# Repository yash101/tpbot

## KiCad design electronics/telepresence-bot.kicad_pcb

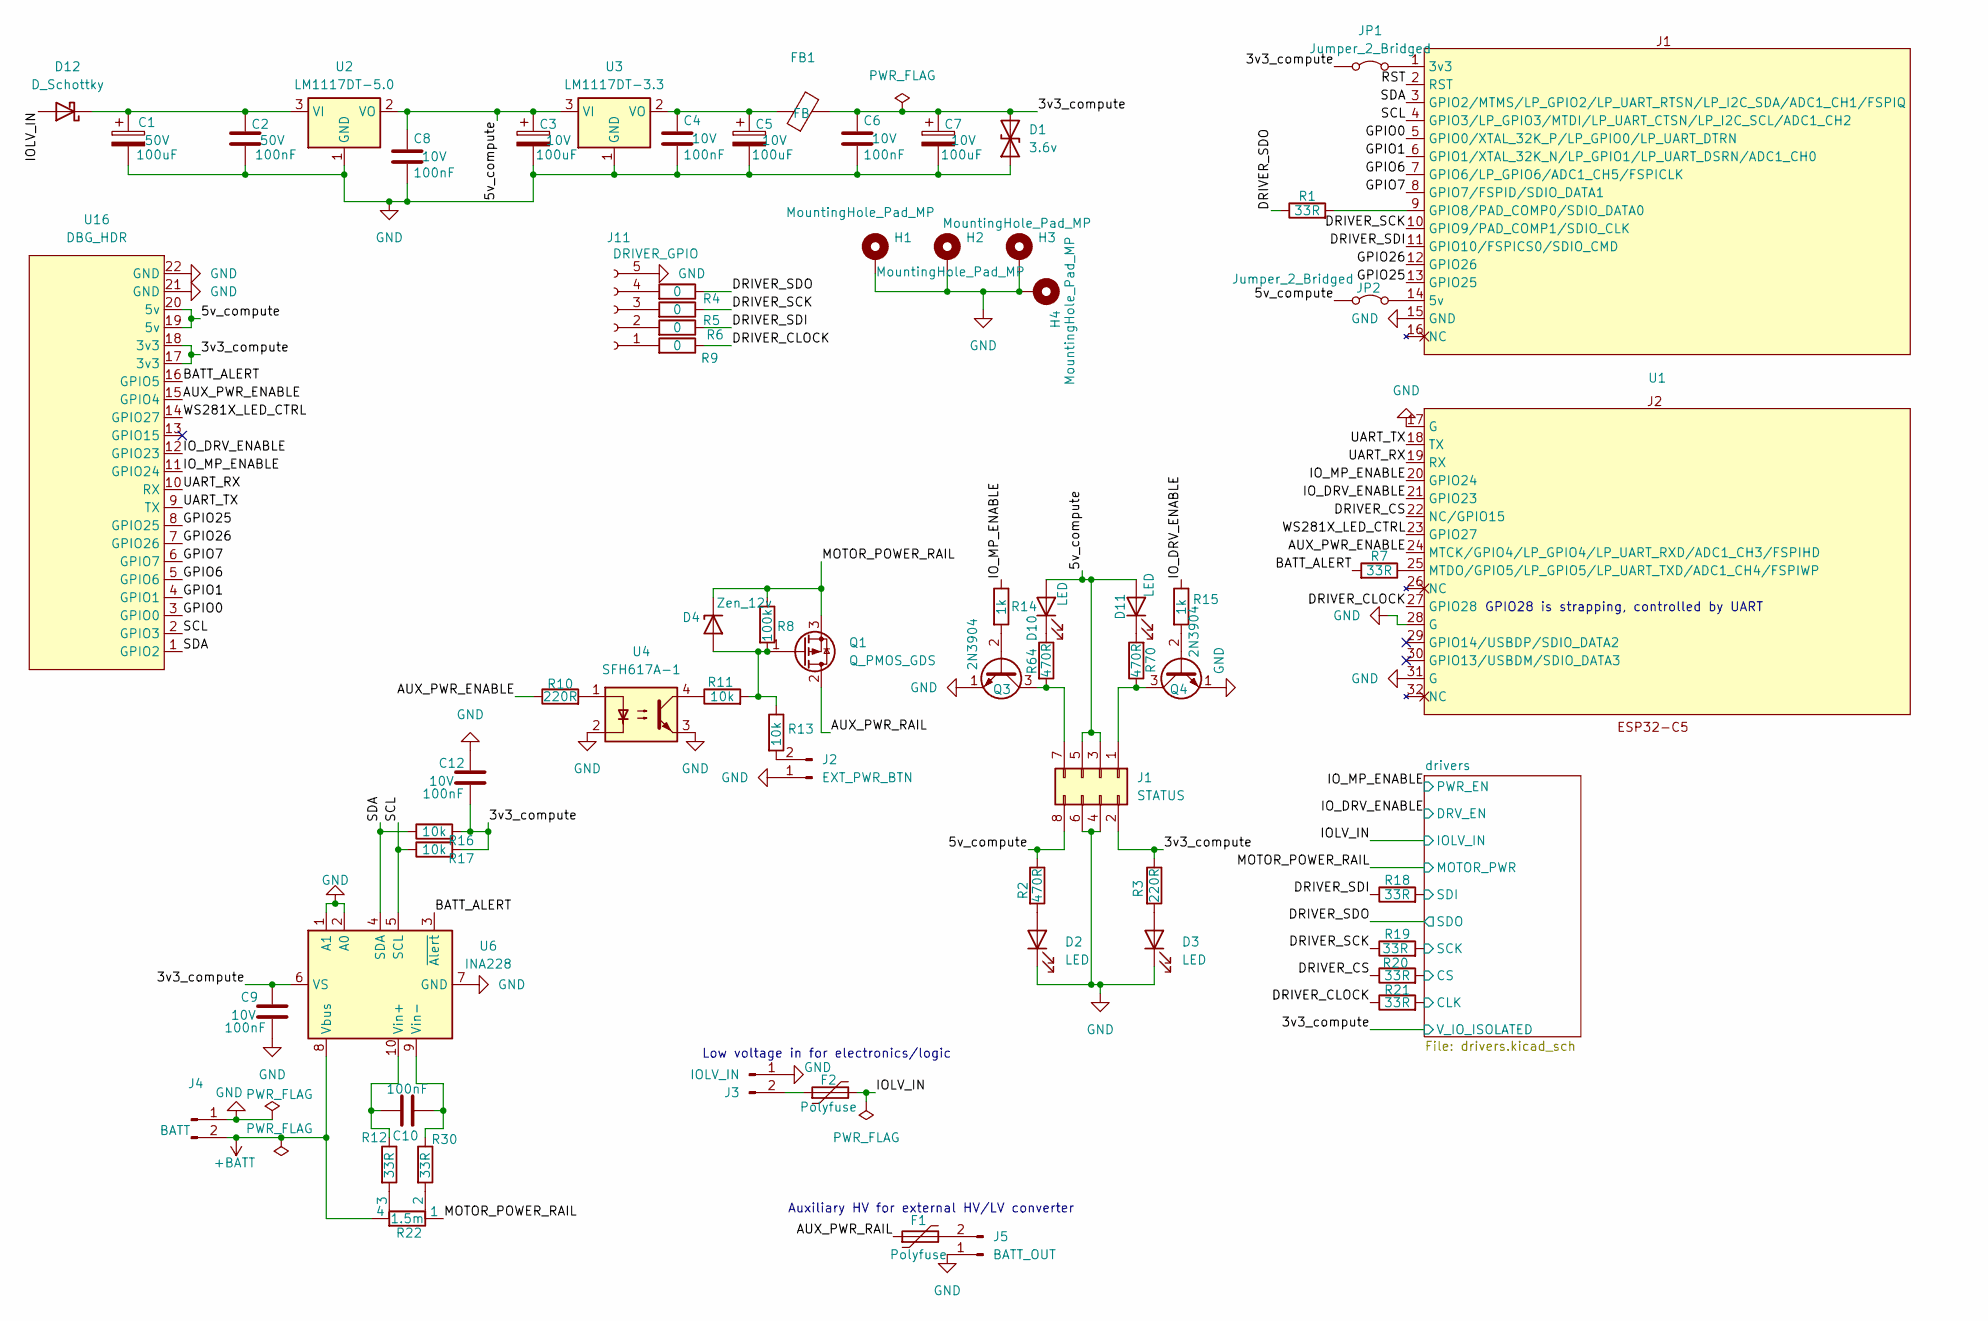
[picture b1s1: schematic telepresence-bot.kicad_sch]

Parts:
C1: 100uF; CP_Radial_D8.0mm_P5.00mm
C2, C10: 100nF; C_1206_3216Metric_Pad1.33x1.80mm_HandSolder
C3, C5, C7: 100uF; CP_Radial_D6.3mm_P2.50mm
C4, C6, C8, C9, C12: 100nF; C_0805_2012Metric_Pad1.18x1.45mm_HandSolder
D1: 3.6v; D_DO-41_SOD81_P2.54mm_Vertical_AnodeUp
D2, D3, D10, D11: LED; LED_D3.0mm
D4: Zen_12v; D_DO-41_SOD81_P2.54mm_Vertical_AnodeUp
D12: D_Schottky; D_DO-201AD_P5.08mm_Vertical_KathodeUp
F1, F2: Polyfuse; RV_Disc_D9mm_W5.2mm_P5mm
FB1: FB; L_1210_3225Metric_Pad1.42x2.65mm_HandSolder
H1, H2, H3, H4: MountingHole_Pad_MP; MountingHole_4.3mm_M4_ISO7380
J1: STATUS; PinSocket_2x04_P2.54mm_Vertical
J2: EXT_PWR_BTN; PinHeader_1x02_P2.54mm_Vertical
J3: IOLV_IN; PinHeader_1x02_P2.54mm_Vertical
J4: BATT; BATT_CONNECTOR
J5: BATT_OUT; PinSocket_1x02_P2.54mm_Vertical
J11: DRIVER_GPIO; PinSocket_1x05_P2.54mm_Vertical
JP1, JP2: Jumper_2_Bridged; PinSocket_1x02_P2.54mm_Vertical
Q1: Q_PMOS_GDS; TO-220-3_Vertical
Q3, Q4: 2N3904; TO-92_Inline_Wide
R1, R7, R12, R18, R19, R20, R21, R30: 33R; R_0805_2012Metric_Pad1.20x1.40mm_HandSolder
R2, R64, R70: 470R; R_Axial_DIN0204_L3.6mm_D1.6mm_P1.90mm_Vertical
R3, R10: 220R; R_Axial_DIN0204_L3.6mm_D1.6mm_P1.90mm_Vertical
R4, R5, R6, R9: 0; SolderJumper-2_P1.3mm_Open_Pad1.0x1.5mm
R8: 100k; R_0805_2012Metric_Pad1.20x1.40mm_HandSolder
R11, R13, R16, R17: 10k; R_0805_2012Metric_Pad1.20x1.40mm_HandSolder
R14, R15: 1k; R_Axial_DIN0204_L3.6mm_D1.6mm_P1.90mm_Vertical
R22: 1.5m; R_Shunt_Vishay_WSKW0612
U1: ESP32-C5-DevKitC-1-v1.2
U2: LM1117DT-5.0; TO-220-3_Vertical
U3: LM1117DT-3.3; TO-220-3_Vertical
U4: SFH617A-1; DIP-4_W7.62mm
U6: INA228; VSSOP-10_3x3mm_P0.5mm
U16: DBG_HDR; PinSocket_2x11_P2.54mm_Vertical

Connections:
+BATT: J4.2, R22.4, U6.8 (Vbus)
/3v3_compute: C6.1, C7.1, C9.1, C12.2, D1.2 (A2), FB1.2, J1.2, JP1.1 (A), R3.1, R16.2, R17.2, U6.6 (VS), U16.17 (3v3), U16.18 (3v3); also elsewhere on the board
/5v_compute: C3.1, C8.1, D10.2 (A), D11.2 (A), J1.3, J1.5, J1.8, JP2.1 (A), R2.1, U2.2 (VO), U3.3 (VI), U16.19 (5v), U16.20 (5v)
/AUX_PWR_ENABLE: R10.1, U1.24 (MTCK/GPIO4/LP_GPIO4/LP_UART_RXD/ADC1_CH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), U16.15 (GPIO4)
/AUX_PWR_RAIL: F1.1, Q1.2 (D)
/BATT_ALERT: R7.2, U6.3 (~Alert), U16.16 (GPIO5)
/DRIVER_CLOCK: R9.1, R21.1, U1.27 (GPIO28)
/DRIVER_CS: R20.1, U1.22 (NC/GPIO15)
/DRIVER_SCK: R5.1, R19.1, U1.10 (GPIO9/PAD_COMP1/SDIO_CLK)
/DRIVER_SDI: R6.1, R18.1, U1.11 (GPIO10/FSPICS0/SDIO_CMD)
/DRIVER_SDO: R1.1, R4.1; also elsewhere on the board
/GPIO0: U1.5 (GPIO0/XTAL_32K_P/LP_GPIO0/LP_UART_DTRN), U16.3 (GPIO0)
/GPIO1: U1.6 (GPIO1/XTAL_32K_N/LP_GPIO1/LP_UART_DSRN/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), U16.4 (GPIO1)
/GPIO6: U1.7 (GPIO6/LP_GPIO6/ADC1_CH5/FSPICLK), U16.5 (GPIO6)
/GPIO7: U1.8 (GPIO7/FSPID/SDIO_DATA1), U16.6 (GPIO7)
/GPIO25: U1.13 (GPIO25), U16.8 (GPIO25)
/GPIO26: U1.12 (GPIO26), U16.7 (GPIO26)
/IOLV_IN: D12.2 (A), F2.2; also elsewhere on the board
/IO_DRV_ENABLE: R15.1, U1.21 (GPIO23), U16.12 (GPIO23); also elsewhere on the board
/IO_MP_ENABLE: R14.1, U1.20 (GPIO24), U16.11 (GPIO24); also elsewhere on the board
/MOTOR_POWER_RAIL: D4.1 (K), Q1.3 (S), R8.1, R22.1; also elsewhere on the board
/RST: U1.2 (RST)
/SCL: R17.1, U1.4 (GPIO3/LP_GPIO3/MTDI/LP_UART_CTSN/LP_I2C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), U6.5 (SCL), U16.2 (GPIO3)
/SDA: R16.1, U1.3 (GPIO2/MTMS/LP_GPIO2/LP_UART_RTSN/LP_I2C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), U6.4 (SDA), U16.1 (GPIO2)
/UART_RX: U1.19 (RX), U16.10 (RX)
/UART_TX: U1.18 (TX), U16.9 (TX)
/WS281X_LED_CTRL: U1.23 (GPIO27), U16.14 (GPIO27)
/drivers/CLK: R21.2; also elsewhere on the board
/drivers/CS: R20.2; also elsewhere on the board
/drivers/SCK: R19.2; also elsewhere on the board
/drivers/SDI: R18.2; also elsewhere on the board
GND: C1.2, C2.2, C3.2, C4.2, C5.2, C6.2, C7.2, C8.2, C9.2, C12.1, D1.1 (A1), D2.1 (K), D3.1 (K), H1.MP, H2.MP, H3.MP, H4.MP, J1.4, J1.6, J2.1, J3.1, J4.1, J5.1, J11.5, Q3.1 (E), Q4.1 (E), U1.15 (GND), U1.17 (G), U1.28 (G), U1.31 (G), U2.1 (GND), U3.1 (GND), U4.2, U4.3, U6.1 (A1), U6.2 (A0), U6.7 (GND), U16.21 (GND), U16.22 (GND); also elsewhere on the board
unnamed: D2.2 (A), R2.2
unnamed: D3.2 (A), R3.2
unnamed: D4.2 (A), Q1.1 (G), R8.2, R11.2, R13.1
unnamed: D10.1 (K), R64.1
unnamed: D11.1 (K), R70.2
unnamed: C1.1, C2.1, D12.1 (K), U2.3 (VI)
unnamed: J1.1, Q4.3 (C), R70.1
unnamed: J1.7, Q3.3 (C), R64.2
unnamed: J2.2, R13.2
unnamed: F2.1, J3.2
unnamed: F1.2, J5.2
unnamed: J11.1, R9.2
unnamed: J11.2, R6.2
unnamed: J11.3, R5.2
unnamed: J11.4, R4.2
unnamed: JP1.2 (B), U1.1 (3v3)
unnamed: JP2.2 (B), U1.14 (5v)
unnamed: Q3.2 (B), R14.2
unnamed: Q4.2 (B), R15.2
unnamed: R10.2, U4.1
unnamed: R11.1, U4.4
unnamed: R12.2, R22.3
unnamed: R22.2, R30.2
unnamed: R1.2, U1.9 (GPIO8/PAD_COMP0/SDIO_DATA0)
unnamed: R7.1, U1.25 (MTDO/GPIO5/LP_GPIO5/LP_UART_TXD/ADC1_CH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)
unnamed: C4.1, C5.1, FB1.1, U3.2 (VO)
unnamed: C10.1, R12.1, U6.10 (Vin+)
unnamed: C10.2, R30.1, U6.9 (Vin-)

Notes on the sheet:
Auxiliary HV for external HV/LV converter
GPIO28 is strapping, controlled by UART
Low voltage in for electronics/logic

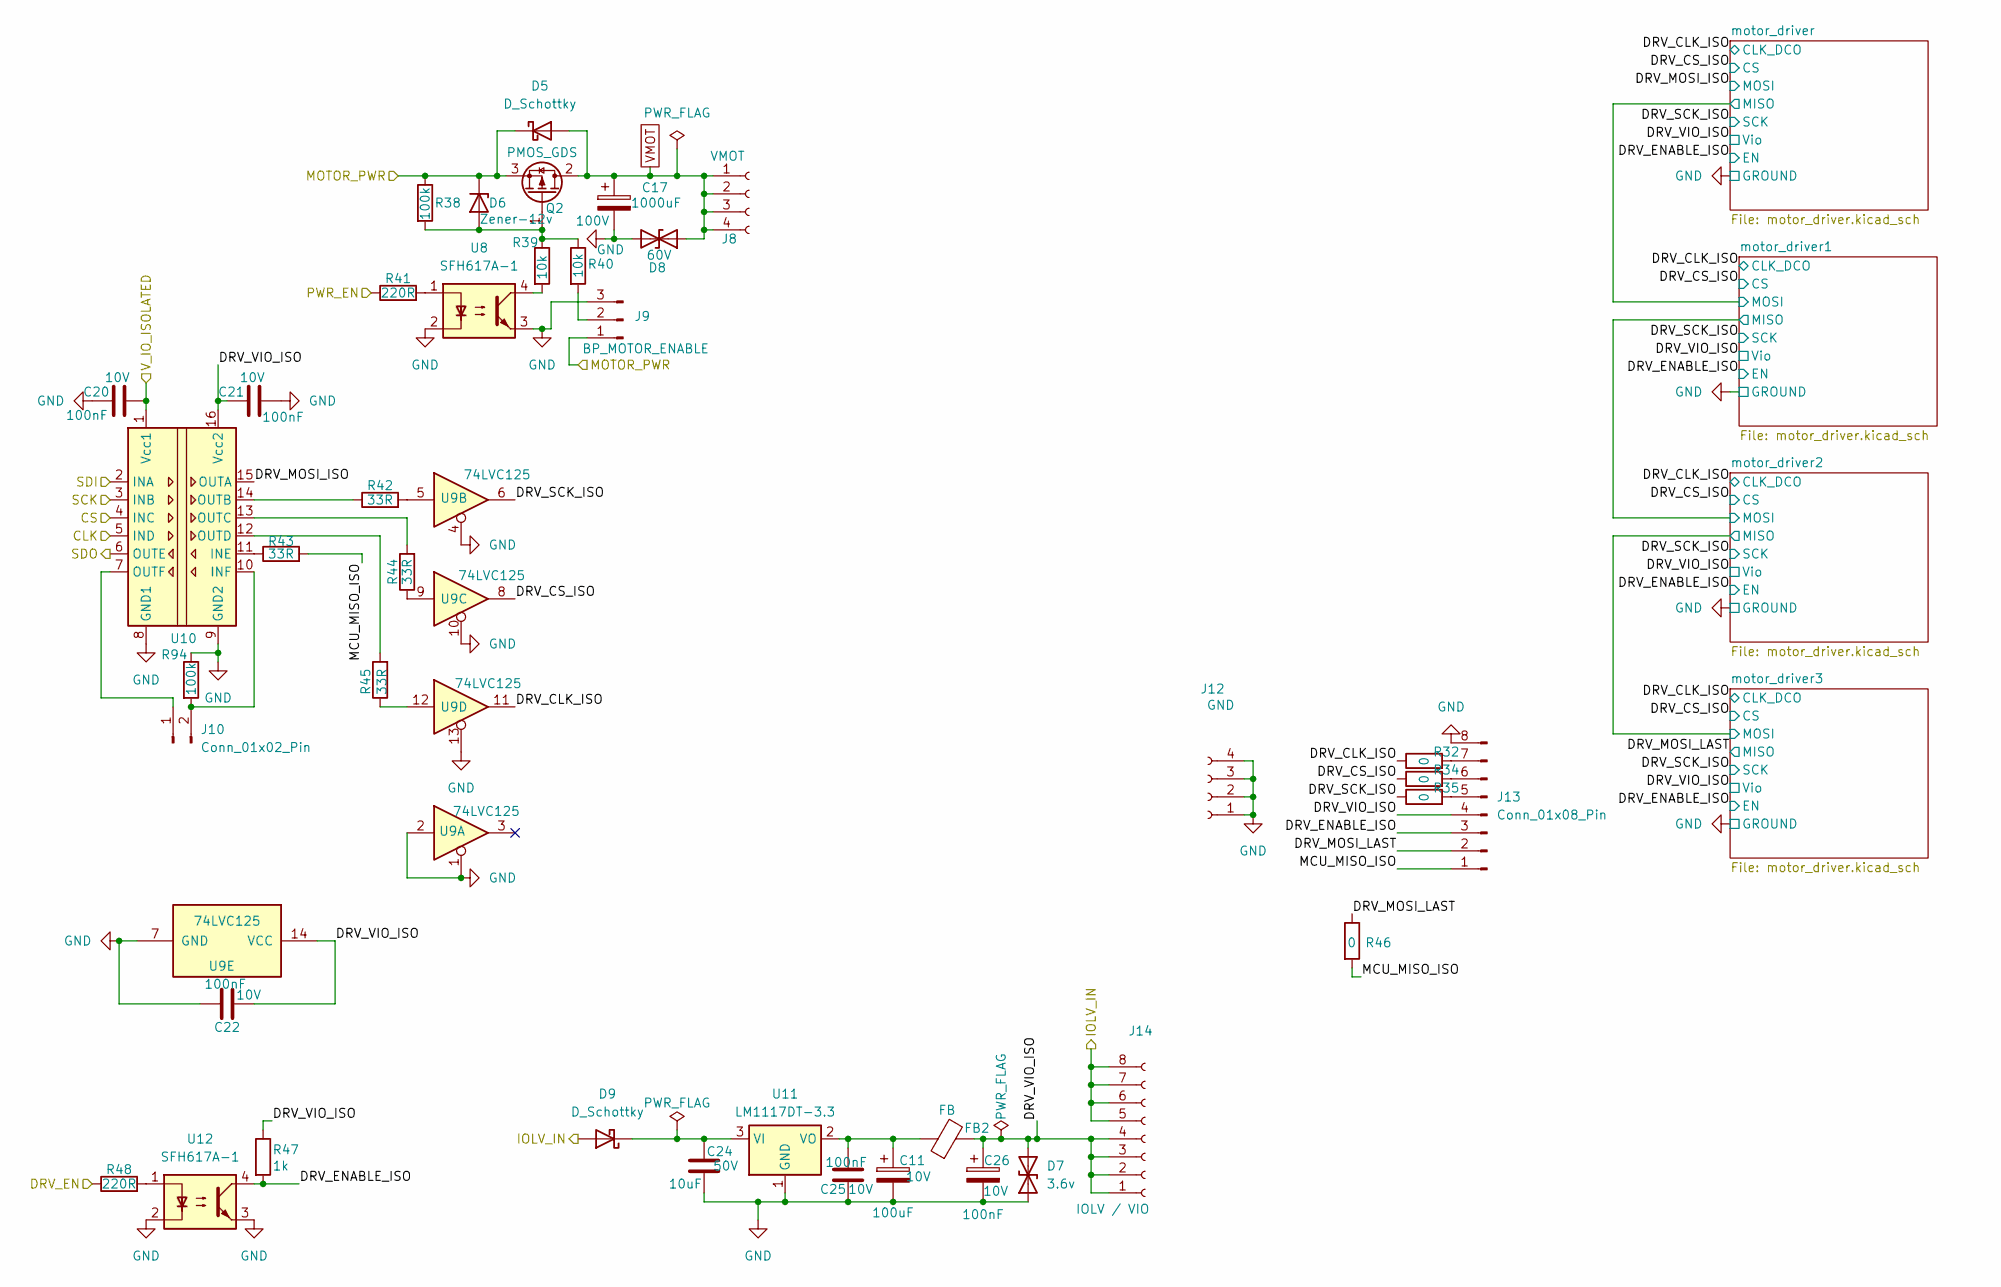
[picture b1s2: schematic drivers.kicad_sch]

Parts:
C11: 100uF; CP_Radial_D6.3mm_P2.50mm
C17: 1000uF; CP_Radial_D18.0mm_P7.50mm
C20, C21, C22, C25, C26: 100nF; C_0805_2012Metric_Pad1.18x1.45mm_HandSolder
C24: 10uF; CP_Radial_D5.0mm_P2.50mm
D5, D9: D_Schottky; D_DO-201AD_P5.08mm_Vertical_KathodeUp
D6: Zener-12v; D_DO-41_SOD81_P2.54mm_Vertical_AnodeUp
D7: 3.6v; D_DO-41_SOD81_P2.54mm_Vertical_AnodeUp
D8: 60V; D_DO-201AD_P5.08mm_Vertical_KathodeUp
FB2: FB; L_1210_3225Metric_Pad1.42x2.65mm_HandSolder
J8: VMOT; PinSocket_1x04_P2.54mm_Vertical
J9: BP_MOTOR_ENABLE; PinSocket_1x03_P2.54mm_Vertical
J10: Conn_01x02_Pin; PinSocket_1x02_P2.54mm_Vertical
J12: GND; PinSocket_1x04_P2.54mm_Vertical
J13: Conn_01x08_Pin; PinSocket_2x04_P2.54mm_Vertical
J14: IOLV / VIO; PinSocket_2x04_P2.54mm_Vertical
Q2: PMOS_GDS; TO-220-3_Vertical
R32, R34, R35, R46: 0; SolderJumper-2_P1.3mm_Open_Pad1.0x1.5mm
R38, R94: 100k; R_0805_2012Metric_Pad1.20x1.40mm_HandSolder
R39, R40: 10k; R_0805_2012Metric_Pad1.20x1.40mm_HandSolder
R41: 220R; R_Axial_DIN0204_L3.6mm_D1.6mm_P2.54mm_Vertical
R42, R43, R44, R45: 33R; R_0805_2012Metric_Pad1.20x1.40mm_HandSolder
R47: 1k; R_Axial_DIN0204_L3.6mm_D1.6mm_P2.54mm_Vertical
R48: 220R; R_Axial_DIN0204_L3.6mm_D1.6mm_P1.90mm_Vertical
U8, U12: SFH617A-1; DIP-4_W7.62mm
U9: 74LVC125; DIP-14_W7.62mm
U10: ISO7762DBQ; SSOP-16_3.9x4.9mm_P0.635mm
U11: LM1117DT-3.3; TO-220-3_Vertical

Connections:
/3v3_compute: C20.2, U10.1 (Vcc1); also elsewhere on the board
/DRIVER_SDO: U10.6 (OUTE); also elsewhere on the board
/IOLV_IN: D9.2 (A), J14.5, J14.6, J14.7, J14.8; also elsewhere on the board
/IO_DRV_ENABLE: R48.1; also elsewhere on the board
/IO_MP_ENABLE: R41.1; also elsewhere on the board
/MOTOR_POWER_RAIL: D5.1 (K), D6.1 (K), J9.1, Q2.3 (S), R38.1; also elsewhere on the board
/drivers/CLK: U10.5 (IND); also elsewhere on the board
/drivers/CS: U10.4 (INC); also elsewhere on the board
/drivers/DRV_CLK_ISO: R32.1, U9.11; also elsewhere on the board
/drivers/DRV_CS_ISO: R34.1, U9.8; also elsewhere on the board
/drivers/DRV_ENABLE_ISO: J13.3, R47.2, U12.4; also elsewhere on the board
/drivers/DRV_MOSI_ISO: U10.15 (OUTA); also elsewhere on the board
/drivers/DRV_MOSI_LAST: J13.2, R46.1; also elsewhere on the board
/drivers/DRV_SCK_ISO: R35.1, U9.6; also elsewhere on the board
/drivers/DRV_VIO_ISO: C21.1, C22.1, C26.1, D7.2 (A2), FB2.2, J13.4, J14.1, J14.2, J14.3, J14.4, R47.1, U9.14 (VCC), U10.16 (Vcc2); also elsewhere on the board
/drivers/MCU_MISO_ISO: J13.1, R43.2, R46.2
/drivers/SCK: U10.3 (INB); also elsewhere on the board
/drivers/SDI: U10.2 (INA); also elsewhere on the board
GND: C11.2, C17.2, C20.1, C21.2, C22.2, C24.2, C25.2, C26.2, D7.1 (A1), D8.2 (A2), J9.3, J12.1, J12.2, J12.3, J12.4, J13.8, R94.1, U8.2, U8.3, U9.1, U9.2, U9.4, U9.7 (GND), U9.10, U9.13, U10.8 (GND1), U10.9 (GND2), U11.1 (GND), U12.2, U12.3; also elsewhere on the board
unnamed: D6.2 (A), Q2.1 (G), R38.2, R39.1, R40.1
unnamed: C24.1, D9.1 (K), U11.3 (VI)
unnamed: J9.2, R40.2
unnamed: J10.1, U10.7 (OUTF)
unnamed: J10.2, R94.2, U10.10 (INF)
unnamed: J13.5, R35.2
unnamed: J13.6, R34.2
unnamed: J13.7, R32.2
unnamed: R39.2, U8.4
unnamed: R41.2, U8.1
unnamed: R42.2, U9.5
unnamed: R44.1, U9.9
unnamed: R45.1, U9.12
unnamed: R48.2, U12.1
unnamed: R43.1, U10.11 (INE)
unnamed: R42.1, U10.14 (OUTB)
unnamed: R44.2, U10.13 (OUTC)
unnamed: R45.2, U10.12 (OUTD)
unnamed: C11.1, C25.1, FB2.1, U11.2 (VO)
VMOT: C17.1, D5.2 (A), D8.1 (A1), J8.1, J8.2, J8.3, J8.4, Q2.2 (D); also elsewhere on the board

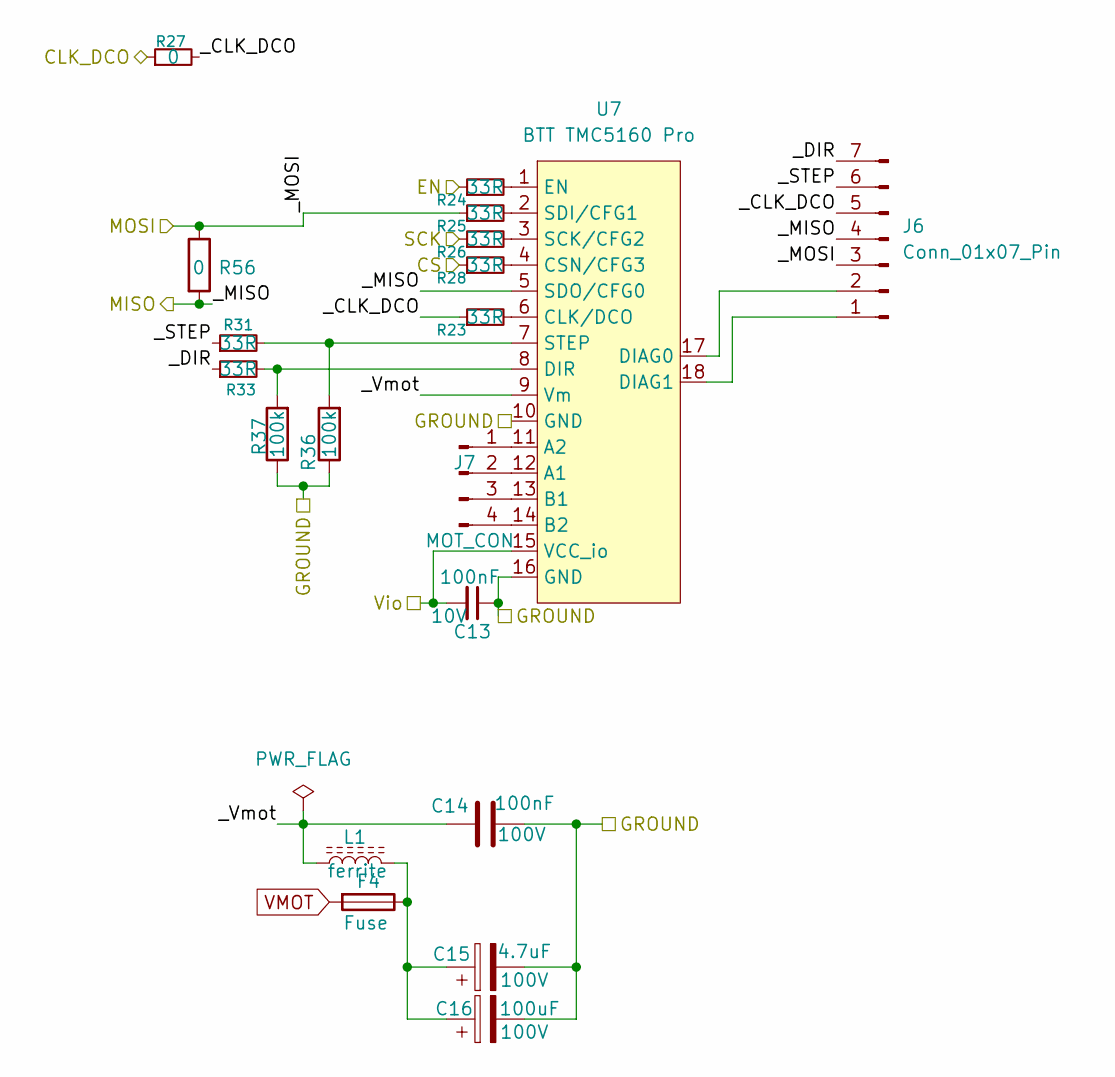
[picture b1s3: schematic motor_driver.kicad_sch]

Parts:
C13: 100nF; C_0805_2012Metric_Pad1.18x1.45mm_HandSolder
C14: 100nF; C_1206_3216Metric_Pad1.33x1.80mm_HandSolder
C15: 4.7uF; CP_Radial_D5.0mm_P2.50mm
C16: 100uF; CP_Radial_D8.0mm_P5.00mm
F4: Fuse; XFCN XF-508P-A-B
J6: Conn_01x07_Pin; PinSocket_1x07_P2.54mm_Vertical
J7: MOT_CON; PinSocket_1x04_P2.54mm_Vertical
L1: ferrite; L_1210_3225Metric_Pad1.42x2.65mm_HandSolder
R23, R24, R25, R26, R28, R31, R33: 33R; R_0805_2012Metric_Pad1.20x1.40mm_HandSolder
R27, R56: 0; SolderJumper-2_P1.3mm_Open_Pad1.0x1.5mm
R36, R37: 100k; R_0805_2012Metric_Pad1.20x1.40mm_HandSolder
U7: BTT TMC5160 Pro; BTT-TMC5160PRO-v1.0

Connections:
/drivers/DRV_CLK_ISO: R27.1; also elsewhere on the board
/drivers/DRV_CS_ISO: R28.1; also elsewhere on the board
/drivers/DRV_ENABLE_ISO: R24.1; also elsewhere on the board
/drivers/DRV_SCK_ISO: R26.1; also elsewhere on the board
/drivers/DRV_VIO_ISO: C13.2, U7.15 (VCC_io); also elsewhere on the board
/drivers/motor_driver1/_CLK_DCO: J6.5, R23.1, R27.2
/drivers/motor_driver1/_DIR: J6.7, R33.1
/drivers/motor_driver1/_MISO: J6.4, R56.2, U7.5 (SDO/CFG0); also elsewhere on the board
/drivers/motor_driver1/_STEP: J6.6, R31.1
/drivers/motor_driver1/_Vmot: C14.1, L1.1, U7.9 (Vm)
/drivers/motor_driver/_MISO: J6.3, R25.1, R56.1; also elsewhere on the board
GND: C13.1, C14.2, C15.2, C16.2, R36.1, R37.1, U7.10 (GND), U7.16 (GND); also elsewhere on the board
unnamed: C15.1, C16.1, F4.1, L1.2
unnamed: J6.1, U7.18 (DIAG1)
unnamed: J6.2, U7.17 (DIAG0)
unnamed: J7.1, U7.11 (A2)
unnamed: J7.2, U7.12 (A1)
unnamed: J7.3, U7.13 (B1)
unnamed: J7.4, U7.14 (B2)
unnamed: R23.2, U7.6 (CLK/DCO)
unnamed: R28.2, U7.4 (CSN/CFG3)
unnamed: R33.2, R37.2, U7.8 (DIR)
unnamed: R24.2, U7.1 (EN)
unnamed: R26.2, U7.3 (SCK/CFG2)
unnamed: R25.2, U7.2 (SDI/CFG1)
unnamed: R31.2, R36.2, U7.7 (STEP)
VMOT: F4.2; also elsewhere on the board

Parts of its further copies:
C27, C31, C35: 100nF; C_0805_2012Metric_Pad1.18x1.45mm_HandSolder
C28, C32, C36: 100nF; C_1206_3216Metric_Pad1.33x1.80mm_HandSolder
C29, C33, C37: 4.7uF; CP_Radial_D5.0mm_P2.50mm
C30, C34, C38: 100uF; CP_Radial_D8.0mm_P5.00mm
F6, F7, F8: Fuse; XFCN XF-508P-A-B
J15, J17, J19: Conn_01x07_Pin; PinSocket_1x07_P2.54mm_Vertical
J16, J18, J20: MOT_CON; PinSocket_1x04_P2.54mm_Vertical
L3, L4, L5: ferrite; L_1210_3225Metric_Pad1.42x2.65mm_HandSolder
R29, R49, R50, R51, R52, R54, R55, R57, R59, R65, R66, R67, R69, R72, R74, R80, R81, R82, R84, R87, R89: 33R; R_0805_2012Metric_Pad1.20x1.40mm_HandSolder
R53, R58, R60, R61, R68, R83: 0; SolderJumper-2_P1.3mm_Open_Pad1.0x1.5mm
R62, R63, R77, R78, R92, R93: 100k; R_0805_2012Metric_Pad1.20x1.40mm_HandSolder
U13, U14, U15: BTT TMC5160 Pro; BTT-TMC5160PRO-v1.0

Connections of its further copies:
/drivers/DRV_CLK_ISO: R53.1, R68.1, R83.1; also elsewhere on the board
/drivers/DRV_CS_ISO: R54.1, R69.1, R84.1; also elsewhere on the board
/drivers/DRV_ENABLE_ISO: R50.1, R65.1, R80.1; also elsewhere on the board
/drivers/DRV_MOSI_ISO: J15.3, R51.1, R58.1; also elsewhere on the board
/drivers/DRV_MOSI_LAST: J19.4, R61.2, U15.5 (SDO/CFG0); also elsewhere on the board
/drivers/DRV_SCK_ISO: R52.1, R67.1, R82.1; also elsewhere on the board
/drivers/DRV_VIO_ISO: C27.2, C31.2, C35.2, U13.15 (VCC_io), U14.15 (VCC_io), U15.15 (VCC_io); also elsewhere on the board
/drivers/motor_driver1/_MISO: J17.3, R60.1, R66.1; also elsewhere on the board
/drivers/motor_driver2/_CLK_DCO: J17.5, R49.1, R68.2
/drivers/motor_driver2/_DIR: J17.7, R74.1
/drivers/motor_driver2/_MISO: J17.4, J19.3, R60.2, R61.1, R81.1, U14.5 (SDO/CFG0)
/drivers/motor_driver2/_STEP: J17.6, R72.1
/drivers/motor_driver2/_Vmot: C32.1, L4.1, U14.9 (Vm)
/drivers/motor_driver3/_CLK_DCO: J19.5, R55.1, R83.2
/drivers/motor_driver3/_DIR: J19.7, R89.1
/drivers/motor_driver3/_STEP: J19.6, R87.1
/drivers/motor_driver3/_Vmot: C36.1, L5.1, U15.9 (Vm)
/drivers/motor_driver/_CLK_DCO: J15.5, R29.1, R53.2
/drivers/motor_driver/_DIR: J15.7, R59.1
/drivers/motor_driver/_MISO: J15.4, R58.2, U13.5 (SDO/CFG0); also elsewhere on the board
/drivers/motor_driver/_STEP: J15.6, R57.1
/drivers/motor_driver/_Vmot: C28.1, L3.1, U13.9 (Vm)
GND: C27.1, C28.2, C29.2, C30.2, C31.1, C32.2, C33.2, C34.2, C35.1, C36.2, C37.2, C38.2, R62.1, R63.1, R77.1, R78.1, R92.1, R93.1, U13.10 (GND), U13.16 (GND), U14.10 (GND), U14.16 (GND), U15.10 (GND), U15.16 (GND); also elsewhere on the board
unnamed: C29.1, C30.1, F6.1, L3.2
unnamed: C33.1, C34.1, F7.1, L4.2
unnamed: C37.1, C38.1, F8.1, L5.2
unnamed: J15.1, U13.18 (DIAG1)
unnamed: J15.2, U13.17 (DIAG0)
unnamed: J16.1, U13.11 (A2)
unnamed: J16.2, U13.12 (A1)
unnamed: J16.3, U13.13 (B1)
unnamed: J16.4, U13.14 (B2)
unnamed: J17.1, U14.18 (DIAG1)
unnamed: J17.2, U14.17 (DIAG0)
unnamed: J18.1, U14.11 (A2)
unnamed: J18.2, U14.12 (A1)
unnamed: J18.3, U14.13 (B1)
unnamed: J18.4, U14.14 (B2)
unnamed: J19.1, U15.18 (DIAG1)
unnamed: J19.2, U15.17 (DIAG0)
unnamed: J20.1, U15.11 (A2)
unnamed: J20.2, U15.12 (A1)
unnamed: J20.3, U15.13 (B1)
unnamed: J20.4, U15.14 (B2)
unnamed: R29.2, U13.6 (CLK/DCO)
unnamed: R54.2, U13.4 (CSN/CFG3)
unnamed: R59.2, R63.2, U13.8 (DIR)
unnamed: R50.2, U13.1 (EN)
unnamed: R52.2, U13.3 (SCK/CFG2)
unnamed: R51.2, U13.2 (SDI/CFG1)
unnamed: R57.2, R62.2, U13.7 (STEP)
unnamed: R49.2, U14.6 (CLK/DCO)
unnamed: R69.2, U14.4 (CSN/CFG3)
unnamed: R74.2, R78.2, U14.8 (DIR)
unnamed: R65.2, U14.1 (EN)
unnamed: R67.2, U14.3 (SCK/CFG2)
unnamed: R66.2, U14.2 (SDI/CFG1)
unnamed: R72.2, R77.2, U14.7 (STEP)
unnamed: R55.2, U15.6 (CLK/DCO)
unnamed: R84.2, U15.4 (CSN/CFG3)
unnamed: R89.2, R93.2, U15.8 (DIR)
unnamed: R80.2, U15.1 (EN)
unnamed: R82.2, U15.3 (SCK/CFG2)
unnamed: R81.2, U15.2 (SDI/CFG1)
unnamed: R87.2, R92.2, U15.7 (STEP)
VMOT: F6.2, F7.2, F8.2; also elsewhere on the board

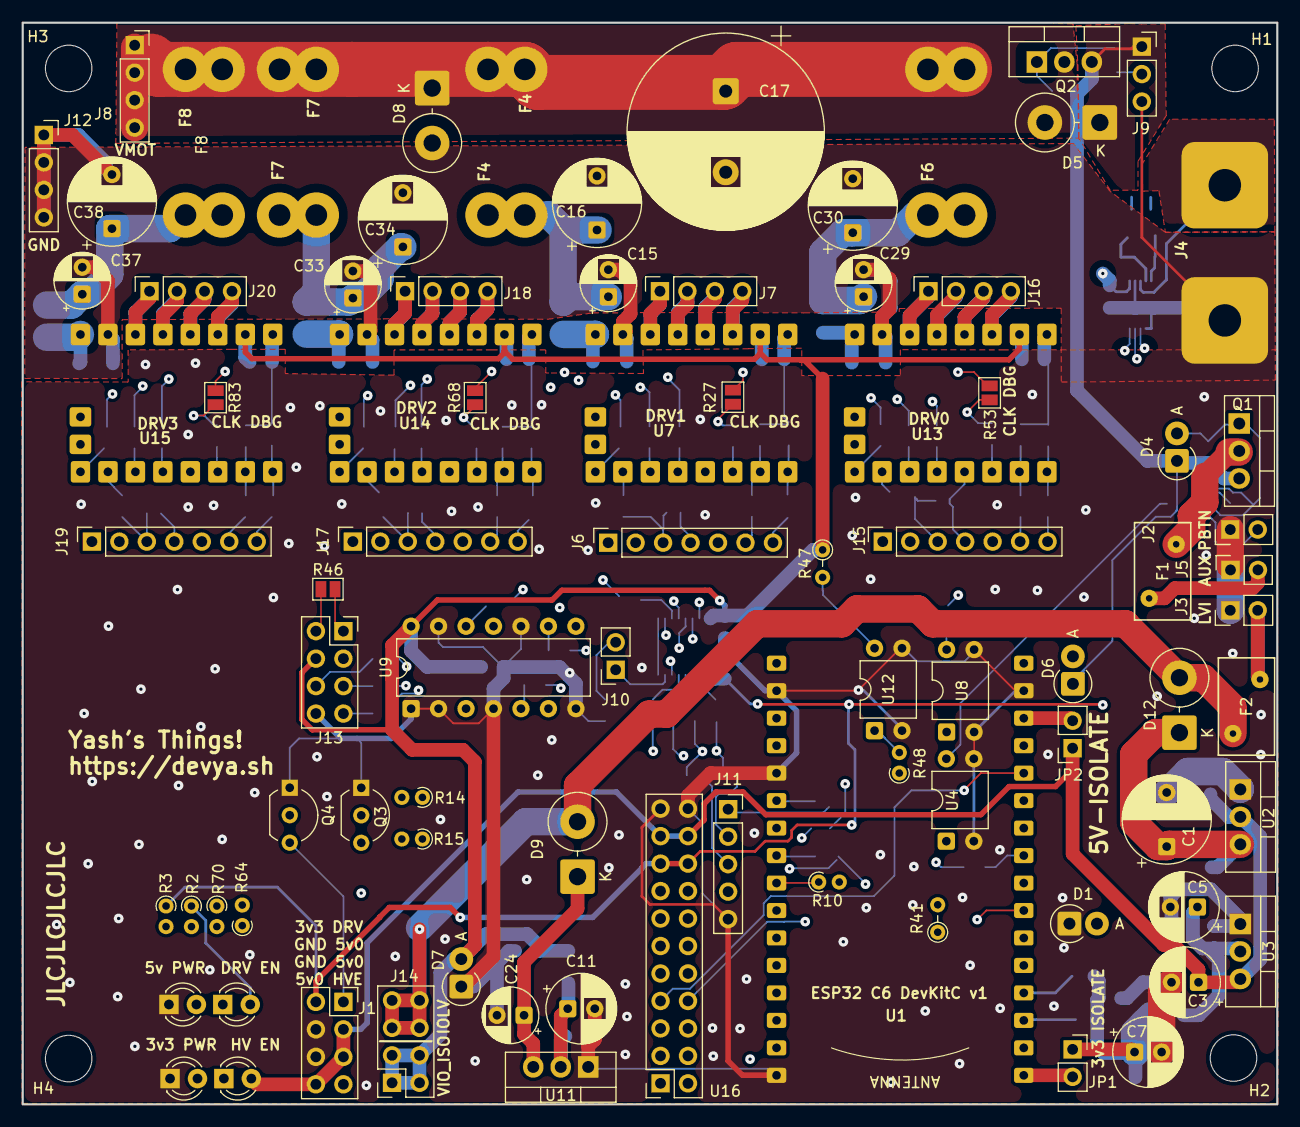
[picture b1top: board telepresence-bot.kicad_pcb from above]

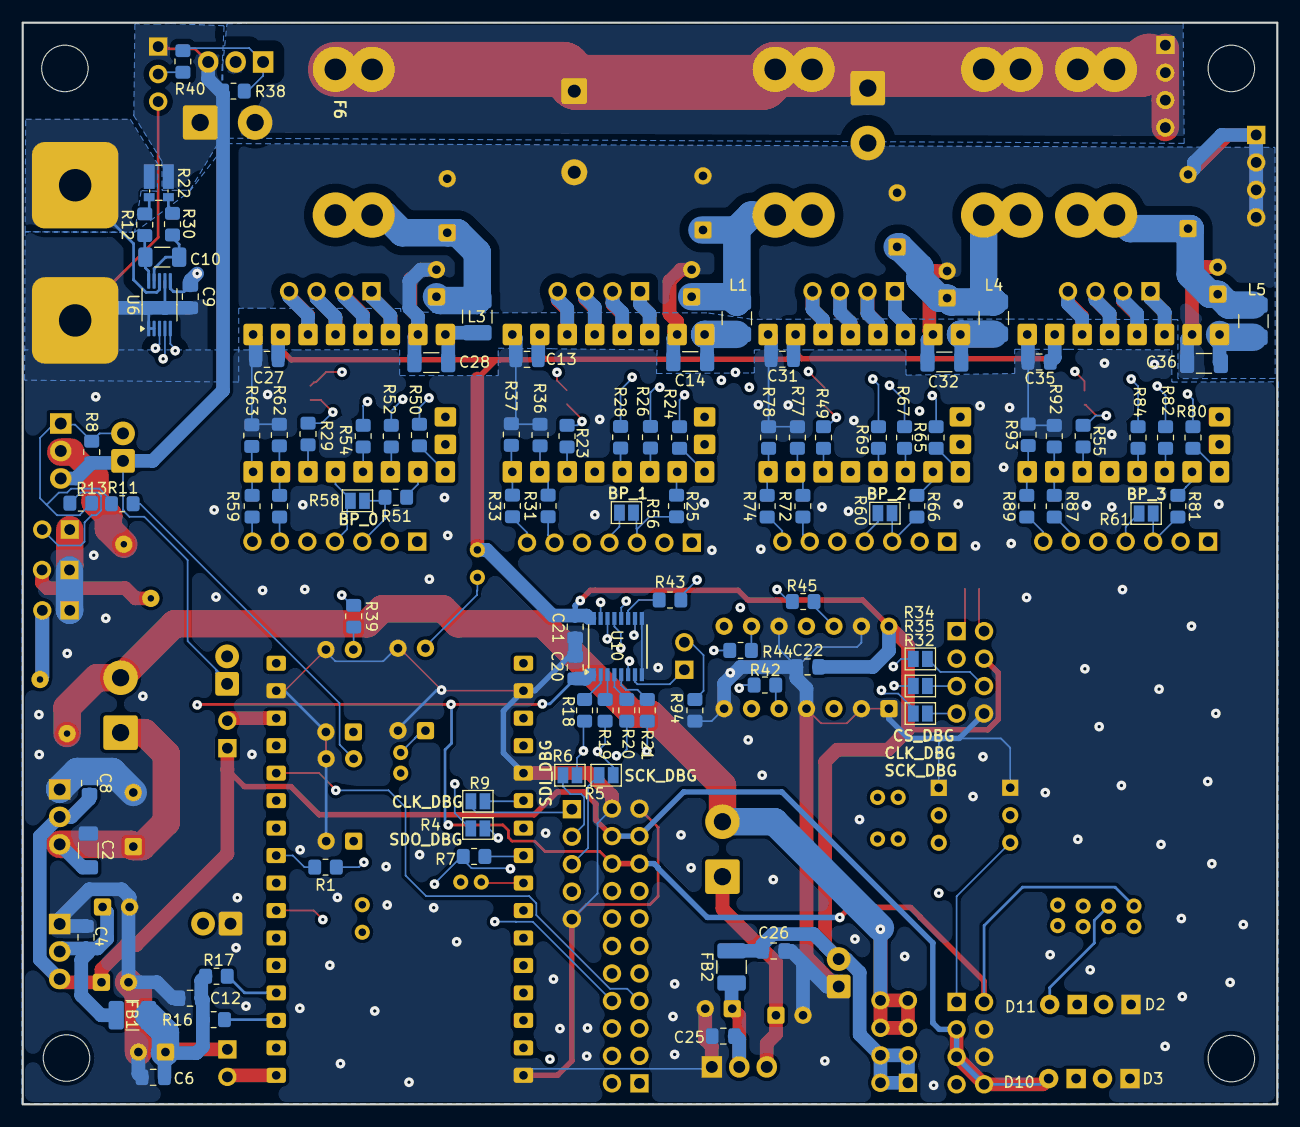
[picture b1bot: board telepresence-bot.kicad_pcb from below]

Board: 4 copper layers, 116.0 x 100.0 mm, 188 parts (97 on the bottom side), 162 nets.

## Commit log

2025-07-23 Checkpoint before switching to 0ohm jumpers
2025-07-29 saving before i nuke this shit
2025-07-30 Switching to a bigger PCB since cost seems negligible
2025-08-20 Updating electronics CAD post-production
2025-08-20 Cleaned up clutter files
2025-08-21 Some vibe coding to set up project structure. Almost all of the code will be rewritten to my standards
2025-08-26 Working on getting this working. Cleaned up a bunch of vibe coded mess and got CMake and maybe libdatachannel working in llbe
2025-08-26 Fixed the submodules
2025-08-27 Got the build mostly working
2025-08-27 Created multicast log terminal and a test tool for multicast
2025-08-29 welp, i've done quite a bit here, almost done with WebRTC with llbe
2025-08-29 cleaned up a bit
2025-08-29 IT BUILT SUCCESSFULLY!
2025-08-31 welp more is coming together
2025-09-01 Starting to look hella
2025-09-02 UI is starting to come together more. Getting more features working.
2025-09-02 More UI improvements
2025-09-02 Working on webrtc now
2025-09-06 Stuff is talking to each other finally
2025-09-08 Commit latest code, lots is working, and there are mocks for when robots are not connected
2026-04-16 uploading latest changes before editing
2026-04-22 most of it's working, checkpointing before starting work on webrtc integration
2026-04-23 saving before letting codex make big changes
2026-04-27 webrtc almost works
2026-04-27 webrtc works but time to pivot to libwebrtc instead
